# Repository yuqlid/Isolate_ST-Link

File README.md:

# Isolate_ST-Link

http://yuqlid.sakura.ne.jp/wp/2017/10/13/isolate_stlink/

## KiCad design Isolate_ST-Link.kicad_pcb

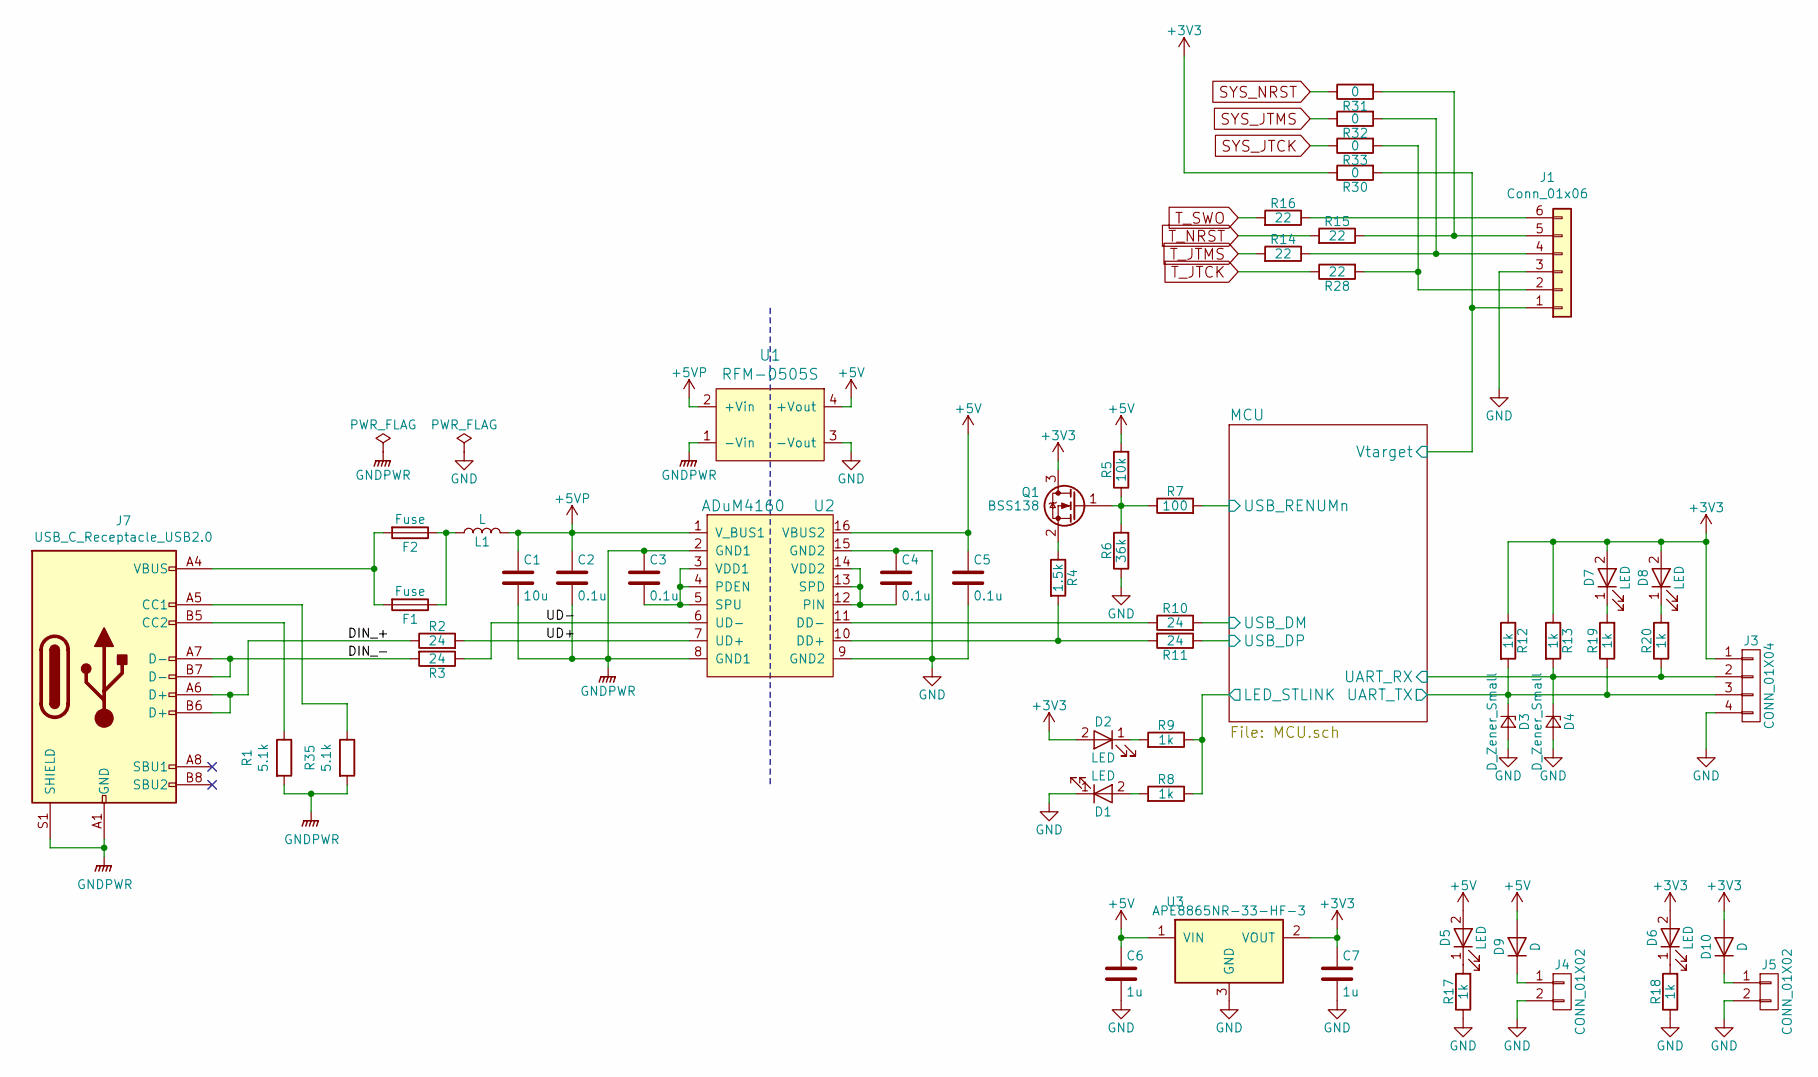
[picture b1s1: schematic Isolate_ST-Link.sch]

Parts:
C1: 10u; C_1206
C2, C3, C4, C5: 0.1u; C_0603_1608Metric
C6, C7: 1u; C_0603_1608Metric
D1, D2, D5, D6, D7, D8: LED; LED_0603_1608Metric
D3, D4: D_Zener_Small; D_SOD-323
D9, D10: D; D_SOD-123F
F1, F2: Fuse; Fuse_0603_1608Metric
J1: Conn_01x06; JST_EH_S6B-EH_1x06_P2.50mm_Horizontal
J3: CONN_01X04; JST_EH_S04B-EH_1x04_P2.50mm_Horizontal
J4, J5: CONN_01X02; JST_EH_S02B-EH_1x02_P2.50mm_Horizontal
J7: USB_C_Receptacle_USB2.0; USB_C_Receptacle_GCT_USB4085
L1: L; L_0603_1608Metric
Q1: BSS138; SOT-23
R1, R35: 5.1k; R_0402_1005Metric
R2, R3, R10, R11: 24; R_0603_1608Metric
R4: 1.5k; R_0603_1608Metric
R5: 10k; R_0603_1608Metric
R6: 36k; R_0603_1608Metric
R7: 100; R_0603_1608Metric
R8, R9, R12, R13, R17, R18, R19, R20: 1k; R_0603_1608Metric
R14, R15, R16, R28: 22; R_0603_1608Metric
R30, R31, R32, R33: 0; R_0603_1608Metric
U1: RFM-0505S; Converter_DCDC_RECOM_RFM-0505S-0.2_THT
U2: ADuM4160; SOIC-16W_7.5x10.3mm_P1.27mm
U3: APE8865NR-33-HF-3; SOT-23

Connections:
+3V3: C7.1, D2.2 (A), D6.2 (A), D7.2 (A), D8.2 (A), D10.2 (A), J3.1, Q1.3 (D), R12.1, R13.1, R30.1, U3.2 (VOUT); also elsewhere on the board
+5V: C5.1, C6.1, D5.2 (A), D9.2 (A), R5.2, U1.4 (+Vout), U2.16 (VBUS2), U3.1 (VIN)
+5VP: C1.1, C2.1, L1.2, U1.2 (+Vin), U2.1 (V_BUS1)
/DIN_+: J7.A6 (D+), J7.B6 (D+), R2.1
/DIN_-: J7.A7 (D-), J7.B7 (D-), R3.2
/MCU/LED_STLINK: R8.1, R9.1; also elsewhere on the board
/MCU/UART_RX: D4.1 (K), J3.2, R13.2, R20.1; also elsewhere on the board
/MCU/UART_TX: D3.1 (K), J3.3, R12.2, R19.1; also elsewhere on the board
/MCU/USB_DM: R10.2; also elsewhere on the board
/MCU/USB_DP: R11.1; also elsewhere on the board
/MCU/USB_RENUMn: R7.2; also elsewhere on the board
/MCU/Vtarget: J1.1, R30.2; also elsewhere on the board
/UD+: R2.2, U2.7 (UD+)
/UD-: R3.1, U2.6 (UD-)
GND: C4.1, C5.2, C6.2, C7.2, D1.1 (K), D3.2 (A), D4.2 (A), J1.3, J3.4, J4.2, J5.2, R6.1, R17.1, R18.1, U1.3 (-Vout), U2.9 (GND2), U2.15 (GND2), U3.3 (GND); also elsewhere on the board
GNDPWR: C1.2, C2.2, C3.1, J7.A1 (GND), J7.A12 (GND), J7.B1 (GND), J7.B12 (GND), J7.S1 (SHIELD), R1.2, R35.2, U1.1 (-Vin), U2.2 (GND1), U2.8 (GND1)
unnamed: C3.2, U2.3 (VDD1), U2.4 (PDEN), U2.5 (SPU)
unnamed: C4.2, U2.12 (PIN), U2.13 (SPD), U2.14 (VDD2)
unnamed: D1.2 (A), R8.2
unnamed: D2.1 (K), R9.2
unnamed: D5.1 (K), R17.2
unnamed: D6.1 (K), R18.2
unnamed: D7.1 (K), R19.2
unnamed: D8.1 (K), R20.2
unnamed: D9.1 (K), J4.1
unnamed: D10.1 (K), J5.1
unnamed: F1.1, F2.1, L1.1
unnamed: F1.2, F2.2, J7.A4 (VBUS), J7.A9 (VBUS), J7.B4 (VBUS), J7.B9 (VBUS)
unnamed: J1.2, R28.2, R33.2
unnamed: J1.4, R14.1, R32.2
unnamed: J1.5, R15.1, R31.2
unnamed: J1.6, R16.1
unnamed: J7.A5 (CC1), R35.1
unnamed: J7.B5 (CC2), R1.1
unnamed: Q1.1 (G), R5.1, R6.2, R7.1
unnamed: Q1.2 (S), R4.1
unnamed: R10.1, U2.11 (DD-)
unnamed: R4.2, R11.2, U2.10 (DD+)
SYS_JTCK: R33.1; also elsewhere on the board
SYS_JTMS: R32.1; also elsewhere on the board
SYS_NRST: R31.1; also elsewhere on the board
T_JTCK: R28.1; also elsewhere on the board
T_JTMS: R14.2; also elsewhere on the board
T_NRST: R15.2; also elsewhere on the board
T_SWO: R16.2; also elsewhere on the board

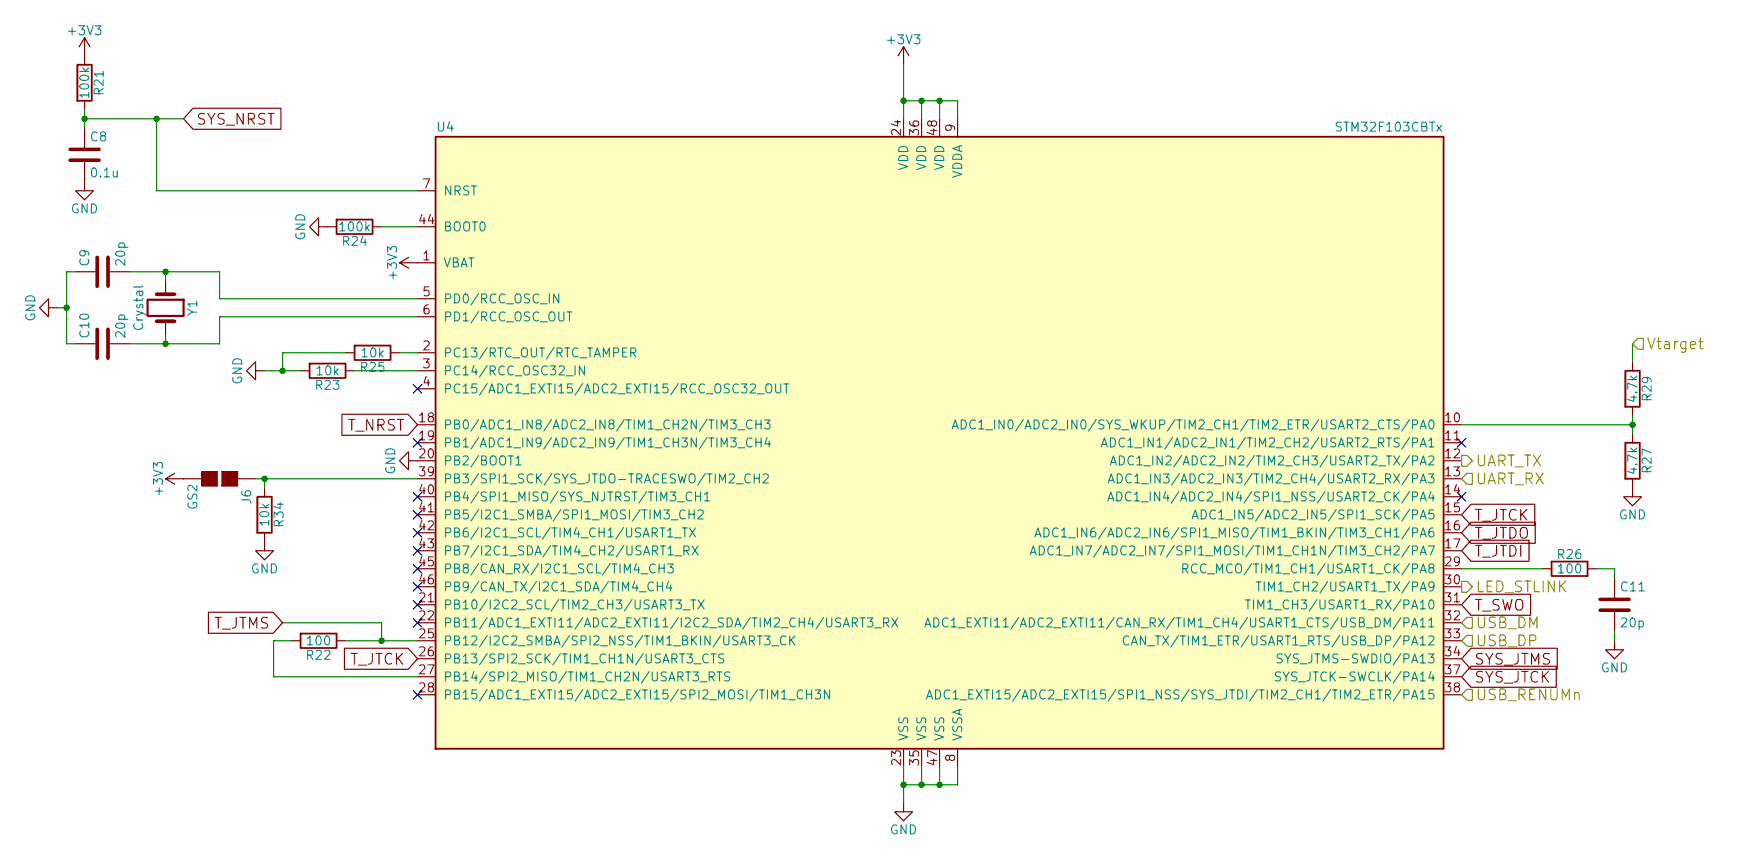
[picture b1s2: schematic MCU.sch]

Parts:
C8: 0.1u; C_0603_1608Metric
C9, C10, C11: 20p; C_0603_1608Metric
J6: GS2; SolderJumper-2_P1.3mm_Open_RoundedPad1.0x1.5mm
R21, R24: 100k; R_0603_1608Metric
R22, R26: 100; R_0603_1608Metric
R23, R25, R34: 10k; R_0603_1608Metric
R27, R29: 4.7k; R_0603_1608Metric
U4: STM32F103CBTx; LQFP-48_7x7mm_P0.5mm
Y1: Crystal; NDK_Crystal_SMD_3225_2Pads

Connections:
+3V3: J6.2 (G2), R21.1, U4.1 (VBAT), U4.9 (VDDA), U4.24 (VDD), U4.36 (VDD), U4.48 (VDD); also elsewhere on the board
/MCU/LED_STLINK: U4.30 (TIM1_CH2/USART1_TX/PA9); also elsewhere on the board
/MCU/UART_RX: U4.13 (ADC1_IN3/ADC2_IN3/TIM2_CH4/USART2_RX/PA3); also elsewhere on the board
/MCU/UART_TX: U4.12 (ADC1_IN2/ADC2_IN2/TIM2_CH3/USART2_TX/PA2); also elsewhere on the board
/MCU/USB_DM: U4.32 (ADC1_EXTI11/ADC2_EXTI11/CAN_RX/TIM1_CH4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); also elsewhere on the board
/MCU/USB_DP: U4.33 (CAN_TX/TIM1_ETR/USART1_RTS/USB_DP/PA12); also elsewhere on the board
/MCU/USB_RENUMn: U4.38 (ADC1_EXTI15/ADC2_EXTI15/SPI1_NSS/SYS_JT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); also elsewhere on the board
/MCU/Vtarget: R29.1; also elsewhere on the board
GND: C8.2, C9.1, C10.1, C11.2, R23.2, R24.2, R25.2, R27.2, R34.2, U4.8 (VSSA), U4.20 (PB2/BOOT1), U4.23 (VSS), U4.35 (VSS), U4.47 (VSS); also elsewhere on the board
unnamed: C9.2, U4.5 (PD0/RCC_OSC_IN), Y1.1
unnamed: C10.2, U4.6 (PD1/RCC_OSC_OUT), Y1.2
unnamed: C11.1, R26.2
unnamed: J6.1 (G1), R34.1, U4.39 (PB3/SPI1_SCK/SYS_JTDO-TRACESWO/TIM2_CH2)
unnamed: R22.2, U4.27 (PB14/SPI2_MISO/TIM1_CH2N/USART3_RTS)
unnamed: R23.1, U4.3 (PC14/RCC_OSC32_IN)
unnamed: R24.1, U4.44 (BOOT0)
unnamed: R25.1, U4.2 (PC13/RTC_OUT/RTC_TAMPER)
unnamed: R26.1, U4.29 (RCC_MCO/TIM1_CH1/USART1_CK/PA8)
unnamed: R27.1, R29.2, U4.10 (ADC1_IN0/ADC2_IN0/SYS_WKUP/TIM2_CH1/TIM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)
SYS_JTCK: U4.37 (SYS_JTCK-SWCLK/PA14); also elsewhere on the board
SYS_JTMS: U4.34 (SYS_JTMS-SWDIO/PA13); also elsewhere on the board
SYS_NRST: C8.1, R21.2, U4.7 (NRST); also elsewhere on the board
T_JTCK: U4.15 (ADC1_IN5/ADC2_IN5/SPI1_SCK/PA5), U4.26 (PB13/SPI2_SCK/TIM1_CH1N/USART3_CTS); also elsewhere on the board
T_JTMS: R22.1, U4.25 (PB12/I2C2_SMBA/SPI2_NSS/TIM1_BKIN/USART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); also elsewhere on the board
T_NRST: U4.18 (PB0/ADC1_IN8/ADC2_IN8/TIM1_CH2N/TIM3_CH3); also elsewhere on the board
T_SWO: U4.31 (TIM1_CH3/USART1_RX/PA10); also elsewhere on the board

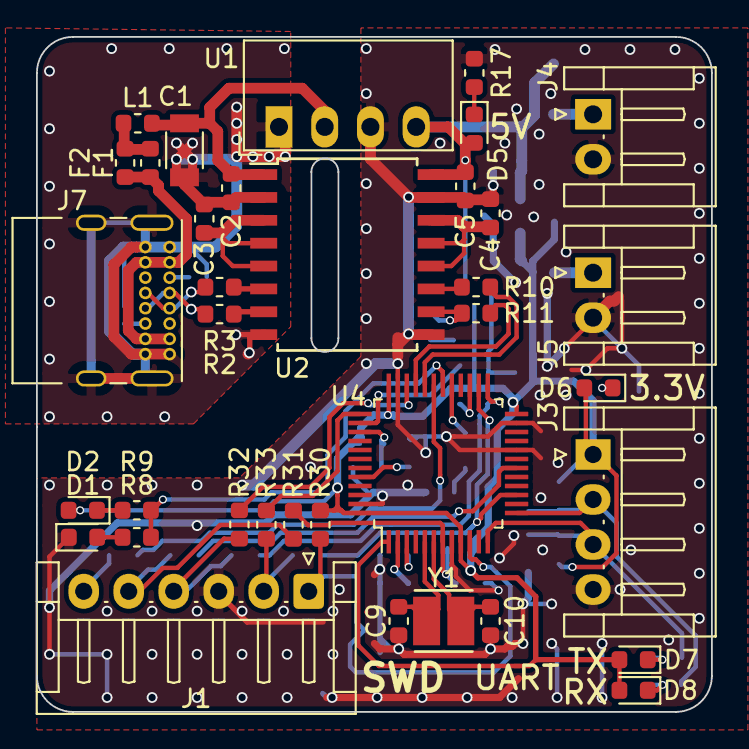
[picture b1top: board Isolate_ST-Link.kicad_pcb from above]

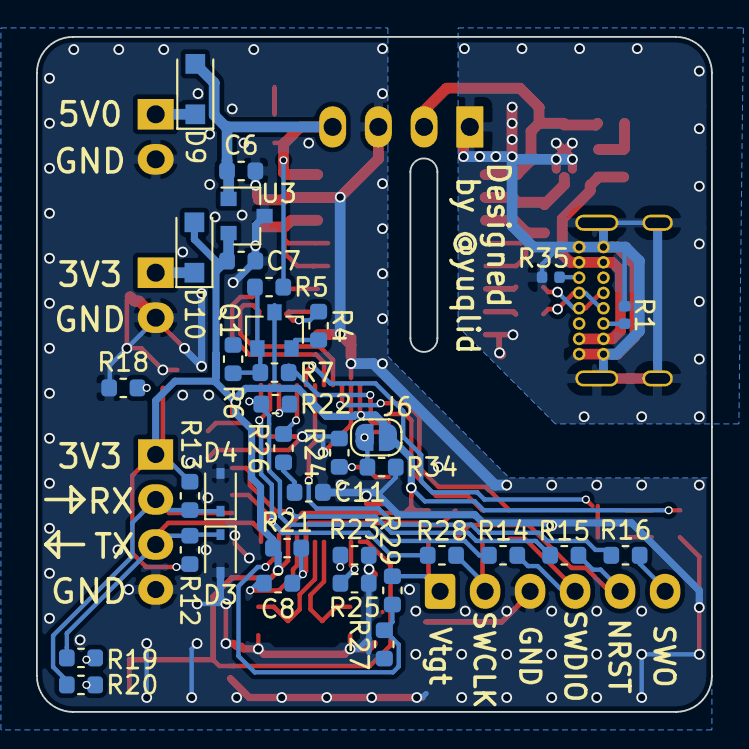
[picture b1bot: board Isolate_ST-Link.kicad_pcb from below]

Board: 2 copper layers, 37.5 x 37.5 mm, 71 parts (35 on the bottom side), 55 nets.

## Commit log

2017-06-20 スピードの切り替えにジャンパを追加
2017-06-20 簡素にした
2017-06-20 基板起こした
2017-06-20 1次側のベタGND作った
2017-06-21 microUSBの参照元を変更
2017-06-21 ツェナーダイオードの参照元を変更
2017-06-21 AW進捗
2017-06-21 完成したのでしばらく寝かせる
2017-06-23 配線の修正
2017-06-26 抵抗のシルクの位置を修正
2017-07-29 Create LICENSE
2017-09-26 ダンピング抵抗追加 分圧抵抗に変更
2017-09-26 部品割当して基板の修正
2017-10-15 https://github.com/Yuqlid/Isolate_ST-Link/projects/1#card-5148549 プルダウン抵抗追加
2017-10-15 書き込みようの抵抗を追加
2017-10-20 AW修正
2017-11-15 UARTのシルクの位置を修正
2017-11-19 見た目を整理
2018-06-08 MicroUSBの位置を少しずらした
2018-08-22 Kicad5.0用に更新，フットプリント変わったのでDRC引っかかりまくった
2019-02-18 DRC全部パスした
2019-02-18 10pin版つくった
2019-04-29 USBをType-Cに
2019-04-29 最低限の配線はできたんじゃね
2019-05-11 DCDCをRECOMのものに変更
2019-05-12 EHコネクタ版
2019-06-15 viaうち職人
